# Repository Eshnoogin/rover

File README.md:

# Version 1

This version of the rover has to be plugged in to work, or be powered by a battery that supplies more than 5 volts. It integrates three motor drivers and a gyroscope to correct for the motors' speeds being slightly off from each other.  It has three almost 3d printed omniwheels, which only need ball bearings and screws. It uses an ESP-32 dev board to drive the motors. It also has ESP-NOW integration, which is needed in order to be driven by an external joystick.

# Version 2 - WIP

This version of the rover supports being completely battery powered with two AA batteries. It is powered by an ESP32-S3, which uses a 3.3 volt regulator. The regulator is also powering the gyroscope and camera *eventually*. Onboard the PCB, there is also a 5v regulator to move the motors. Unlike V1 of the rover, these wheels are completely 3d printed. Unfortunatly, as of right now, the USB connection stopped working after a short and the motors are stuck spinning until shutdown.

# Board 

Version 2 of the board has four layers, with the two internal planes being ground planes, unlike version 1, which just has two layers and a ground fill on each. It uses a Texas Instraments DRV8832DGQR and TPS61040DBVRG4 to drive the motors and boost voltage, respectively. The gyroscope being used is part of the MPU-6050 and, of course, the main component of V2 is the ESP32-S3-WROOM module.

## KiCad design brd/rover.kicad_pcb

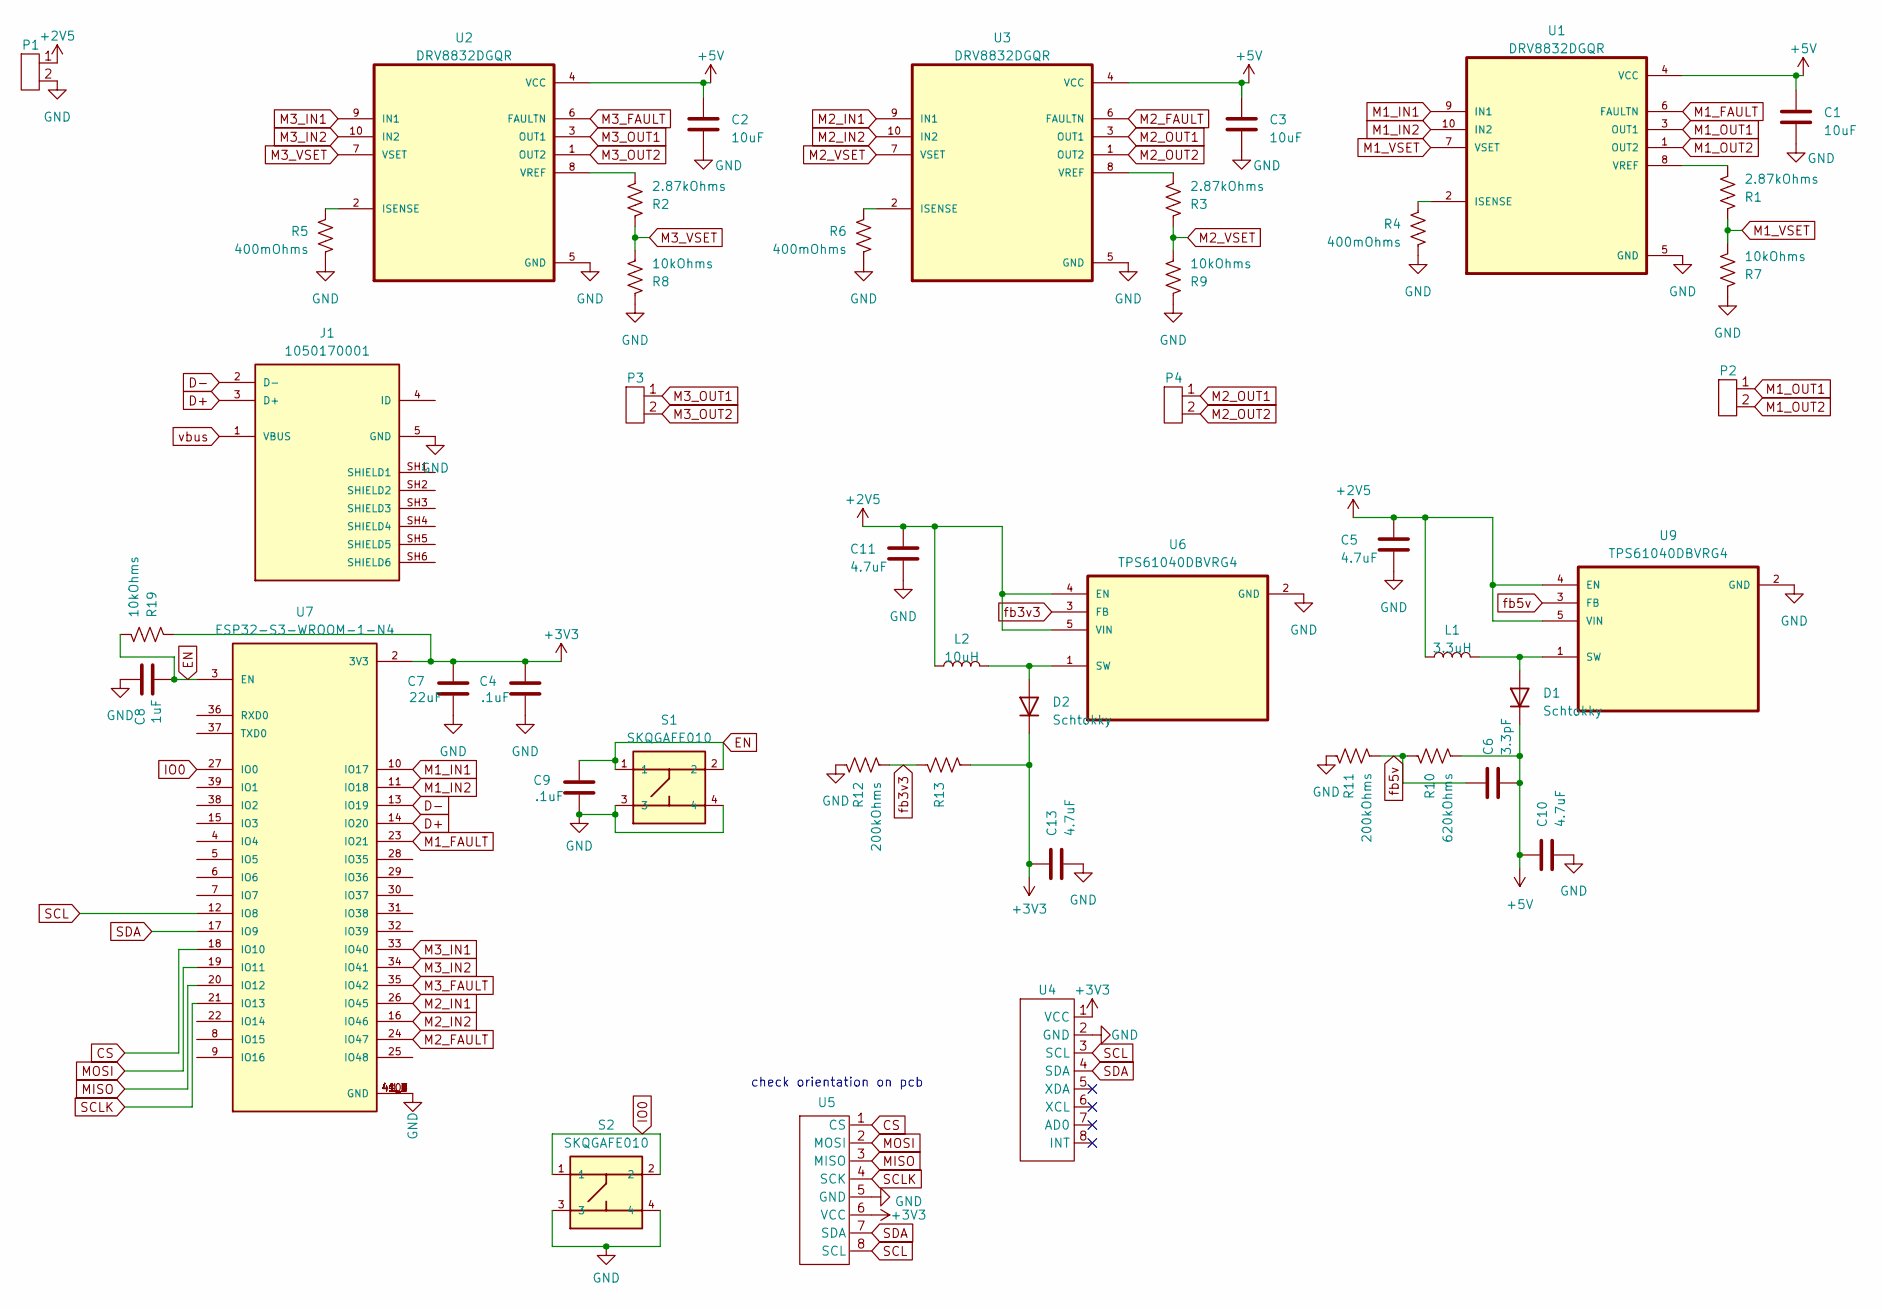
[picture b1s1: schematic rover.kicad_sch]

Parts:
C1, C2, C3: 10uF; cap1206
C4, C9: .1uF; cap1206
C5, C10, C11, C13: 4.7uF; cap1206
C6: 3.3pF; cap1206
C7: 22uF; cap1206
C8: 1uF; cap1206
D1, D2: Schtokky; D_SOD-123
J1: 1050170001; MOLEX_1050170001; PARTREV F
L1: 3.3uH; IND_SRR1240-100M
L2: 10uH; IND_SRR1240-100M
P1: PinHeader_1x02_P2.54mm_Vertical
P2, P3, P4: twopad
R1, R2, R3: 2.87kOhms; res1206
R4, R5, R6: 400mOhms; res1206
R7, R8, R9, R19: 10kOhms; res1206
R10: 620kOhms; res1206
R11, R12: 200kOhms; res1206
R13: 330kOhms; res1206
S1, S2: SKQGAFE010; SW_SKQGAFE010; PART_REV B1
U1, U2, U3: DRV8832DGQR; IC_XTR111AIDGQRG4
U4, U5: PinSocket_1x08_P2.54mm_Vertical
U6, U9: TPS61040DBVRG4; SOT95P280X145-5N
U7: ESP32-S3-WROOM-1-N4; XCVR_ESP32S3WROOM1N8R8; PARTREV v1.0

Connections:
+2V5: C5.1, C11.1, L1.1, L2.1, P1.1, U6.4 (EN), U6.5 (VIN), U9.4 (EN), U9.5 (VIN)
+3V3: C4.1, C7.1, C13.1, D2.1 (K), R13.2, R19.1, U4.1 (VCC), U5.6 (VCC), U7.2 (3V3)
+5V: C1.1, C2.1, C3.1, C6.2, C10.1, D1.1 (K), R10.2, U1.4 (VCC), U2.4 (VCC), U3.4 (VCC)
CS: U5.1 (CS), U7.18 (IO10)
D+: J1.3 (D+), U7.14 (IO20)
D-: J1.2 (D-), U7.13 (IO19)
EN: C8.2, C9.1, R19.2, S1.1, S1.2, U7.3 (EN)
GND: C1.2, C2.2, C3.2, C4.2, C5.2, C7.2, C8.1, C9.2, C10.2, C11.2, C13.2, J1.5 (GND), P1.2, R4.2, R5.2, R6.2, R7.1, R8.1, R9.1, R11.1, R12.1, S1.3, S1.4, S2.3, S2.4, U1.5 (GND), U2.5 (GND), U3.5 (GND), U4.2 (GND), U5.5 (GND), U6.2 (GND), U7.1 (GND), U7.40 (GND), U7.41_1 (GND), U7.41_2 (GND), U7.41_3 (GND), U7.41_4 (GND), U7.41_5 (GND), U7.41_6 (GND), U7.41_7 (GND), U7.41_8 (GND), U7.41_9 (GND), U9.2 (GND)
IO0: S2.1, S2.2, U7.27 (IO0)
M1_FAULT: U1.6 (FAULTN), U7.23 (IO21)
M1_IN1: U1.9 (IN1), U7.10 (IO17)
M1_IN2: U1.10 (IN2), U7.11 (IO18)
M1_OUT1: P2.1, U1.3 (OUT1)
M1_OUT2: P2.2, U1.1 (OUT2)
M1_VSET: R1.1, R7.2, U1.7 (VSET)
M2_FAULT: U3.6 (FAULTN), U7.24 (IO47)
M2_IN1: U3.9 (IN1), U7.26 (IO45)
M2_IN2: U3.10 (IN2), U7.16 (IO46)
M2_OUT1: P4.1, U3.3 (OUT1)
M2_OUT2: P4.2, U3.1 (OUT2)
M2_VSET: R3.1, R9.2, U3.7 (VSET)
M3_FAULT: U2.6 (FAULTN), U7.35 (IO42)
M3_IN1: U2.9 (IN1), U7.33 (IO40)
M3_IN2: U2.10 (IN2), U7.34 (IO41)
M3_OUT1: P3.1, U2.3 (OUT1)
M3_OUT2: P3.2, U2.1 (OUT2)
M3_VSET: R2.1, R8.2, U2.7 (VSET)
MISO: U5.3 (MISO), U7.20 (IO12)
MOSI: U5.2 (MOSI), U7.19 (IO11)
unnamed: D1.2 (A), L1.2, U9.1 (SW)
unnamed: D2.2 (A), L2.2, U6.1 (SW)
unnamed: R4.1, U1.2 (ISENSE)
unnamed: R1.2, U1.8 (VREF)
unnamed: R5.1, U2.2 (ISENSE)
unnamed: R2.2, U2.8 (VREF)
unnamed: R6.1, U3.2 (ISENSE)
unnamed: R3.2, U3.8 (VREF)
SCL: U4.3 (SCL), U5.8 (SCL), U7.12 (IO8)
SCLK: U5.4 (SCK), U7.21 (IO13)
SDA: U4.4 (SDA), U5.7 (SDA), U7.17 (IO9)
fb3v3: R12.2, R13.1, U6.3 (FB)
fb5v: C6.1, R10.1, R11.2, U9.3 (FB)
vbus: J1.1 (VBUS)

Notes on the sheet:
check orientation on pcb

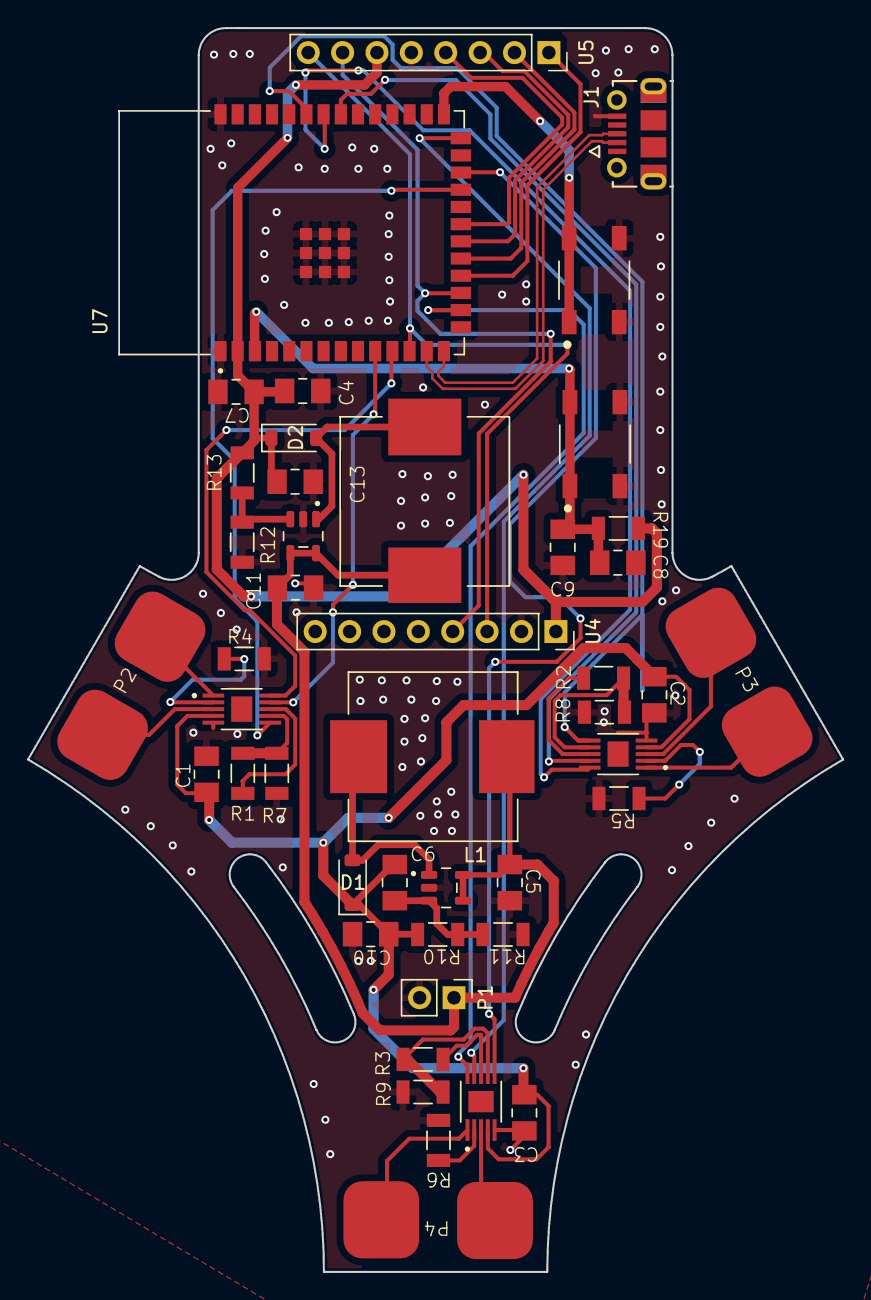
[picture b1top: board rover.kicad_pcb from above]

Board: 4 copper layers, 60.2 x 91.9 mm, 45 parts (0 on the bottom side), 42 nets.

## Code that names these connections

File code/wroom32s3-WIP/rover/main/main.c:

#include <stdio.h>
#include <math.h>

#include "freertos/FreeRTOS.h"
#include "esp_log.h"
#include "driver/i2c_master.h"
#include "driver/mcpwm_timer.h"
#include "driver/mcpwm_oper.h"
#include "driver/mcpwm_gen.h"
#include "driver/mcpwm_cmpr.h"
#include "esp_timer.h"

#include "driver/gpio.h"

#include "imu.h"
#include "common.h"
#include "motor.h"
#include "comm.h"

#define TAG "RVR"

#define M1_IN1 17
#define M1_IN2 18
#define M1_FAULT 21

#define M2_IN1 45
#define M2_IN2 46
#define M2_FAULT 47

#define M3_IN1 40
#define M3_IN2 41
#define M3_FAULT 42


i2c_master_bus_handle_t i2c_mst_bus_handle;

imu_handle_t imu;

motor_handle_t motor1;
motor_handle_t motor2;
motor_handle_t motor3;

float measured_z_rotation;
SemaphoreHandle_t z_rot_mutex;

void handle_imu()
{
    while (1)
    {
        imu_update_gyro(&imu);

        CRITICAL_SECTION(imu.imu_mutex, 15, {
            CRITICAL_SECTION(z_rot_mutex, 15, {
                if (fabs(imu.gyro_z) > 10){ // some noise will be present in the raw sensor data
                    measured_z_rotation += imu.gyro_z;
                }
            });
        });

        vTaskDelay(10 / portTICK_PERIOD_MS);
    }
}

void handle_movement()
{
    while (1)
    {
        float v1 = 0;
        float v2 = 0;
        float v3 = 0;

        // read gyroscope data
        CRITICAL_SECTION(imu.imu_mutex, 15, {
            bool do_move = true;
            CRITICAL_SECTION(z_rot_mutex, 15, {
                if(fabs(measured_z_rotation) < 300){
                    do_move = false;
                }
                if(do_move){
                    if(fabs(measured_z_rotation) < 450){ //helps the robot face the center in less steps
                        v1 += (measured_z_rotation < 0) ? -0.25 : 0.25;
                        v2 += (measured_z_rotation < 0) ? -0.25 : 0.25;
                        v3 += (measured_z_rotation < 0) ? -0.25 : 0.25;     
                    }else{  
                        v1 += (measured_z_rotation < 0) ? -0.5 : 0.5;
                        v2 += (measured_z_rotation < 0) ? -0.5 : 0.5;
                        v3 += (measured_z_rotation < 0) ? -0.5 : 0.5;        
                    }
                }
            });
        });

        // read espnow data
        CRITICAL_SECTION(last_command.cmd_mutex, 15, {
            if(last_command.time + 20000 > esp_timer_get_time()){
                v1 += cos(last_command.direction);
                v2 += -.5 * cos(last_command.direction) + ((sqrt(3) / 2) * sin(last_command.direction));
                v3 += -.5 * cos(last_command.direction) - ((sqrt(3) / 2) * sin(last_command.direction));

                // normalize values
                float v_max = fmax(fabs(v1), fmax(fabs(v2), fabs(v3)));
                if (v_max != 0)
                {
                    v1 /= v_max;
                    v2 /= v_max;
                    v3 /= v_max;
                }
            }
        });

        ESP_LOGI(TAG, "M1: %f M2: %f M3: %f", v1, v2, v3);

        // move motors
        motor_move_at(&motor1, v1);
        motor_move_at(&motor2, v2);
        motor_move_at(&motor3, v3);

        vTaskDelay(pdMS_TO_TICKS(25));
    }
}

void app_main(void)
{
    // Setup GPIO 17 as output
    gpio_config_t io_conf;
    io_conf.intr_type = GPIO_INTR_DISABLE;   // Disable interrupt
    io_conf.mode = GPIO_MODE_OUTPUT;         // Set as output mode
    io_conf.pin_bit_mask = (1ULL << M1_IN1) | (1ULL << M1_IN2) | (1ULL << M2_IN1) | (1ULL << M2_IN2) | (1ULL << M3_IN1) | (1ULL << M3_IN2);     // Bit mask of the pins to set
    io_conf.pull_down_en = GPIO_PULLDOWN_ENABLE;                // Disable pull-down mode
    io_conf.pull_up_en = 0;                  // Disable pull-up mode
    gpio_config(&io_conf);

    gpio_set_level(M1_IN1, 1);
}

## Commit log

2024-07-18 esp32s3 updates
